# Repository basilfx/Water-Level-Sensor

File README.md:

# Water Level Sensor
Capacitive water level sensor based on a custom Arduino-based board.

## Introduction
This project started as an experiment to see if a water level sensor (with
fixed intervals) could be built, using the Arduino
[ADCTouch](https://github.com/martin2250/ADCTouch) library and capacitive
sensors. Capacitive sensors have the advantage that they can be isolated from
water, creating a water-tight sensor.

In this repository, you can find the CAD designs, firmware and 3D printed
parts to create a water level sensor.

## Features
* Small board that finds in a 19mm tube.
* 4 channels/board, can be daisy-chained up to 8 boards.
* I2C connection.
* Temperature sensor.

## Contents
* The `3d/` folder contains a 3D-printable designs for the necessary parts.
* The `applications/` folder contain applications and drivers that can interact
  with the sensor.
* The `firmware/` folder contains the Platform.IO-based firmware that runs on
  the sensors.
* The `pcb/` folder contains the Kicad schema and board design.

## My setup
Several proof of concepts have been built, to validate the idea and the
sensitivity of the setup in a 19mm PVC pipe (electrical conduit pipe). This
pipe was perfect for my 400 liter rain barrel, only occupying 0.5 L of water.

To create the fixed intervals, I 3D printed coils that I wound using 1.5 mm²
electrical wire. I could not get copper/aluminium tube that fitted exactly in
the 19mm tube, and this 'solution' somewhat expands against the inside of the
tube, ensuring as little as possible air between the tube and the coil.

In total, I used 4 sensor boards, connecting a total of 16 intervals, or
25 liter per interval. The picture below shows render of how one sensor board
is used for four intervals. Four of these assemblies are daisy-chained
together. The parent board is then connected to an external application to
read the sensor.

## License
The work in this repository is covered by CC BY-NC-SA 4.0. See the `LICENSE.md`
file for more information.

Some parts of this project are covered by a different license.

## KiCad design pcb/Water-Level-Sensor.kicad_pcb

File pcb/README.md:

# Water Level Sensor

## Pictures

## Schema
You can find the schema [here](Water-Level-Sensor.pdf).

## Mode of operation
The same board can operate in two modes:

* Parent mode
* Child mode

A chain of sensors (maximum of 7 + 1 sensors) exists out of one parent and zero
or more children. The parent will be the interface to the external application.
All children can be daisy-chained together.

```
[Application} <--> [Parent} <--> [Child 1] <--> [Child 2] <--> [Child 3]
```

Depending on the mode of operation, resistors R7-R10 must be populated
accordingly. All children are connected using a separate I2C bus.

The firmware uses R1-R3 and R11 for configuration. As of writing, the following
jumper resistors must be placed for the specific mode of operation.

| R1 | R2 | R3 | R11 | Description
|----|----|----|-----|--------------------------|
|    |    |    | X   | Parent mode, no children |
| X  |    |    | X   | Parent mode, 1 child     |
|    | X  |    | X   | Parent mode, 2 children  |
| X  | X  |    | X   | Parent mode, 3 children  |
|    |    |    |     | Child mode, first child  |
| X  |    |    |     | Child mode, second child |
|    | X  |    |     | Child mode, third child  |
| X  | X  |    |     | Child mode, fourth child |

## BOM
| Ref  | Value         | Footprint                                           | Farnell | DigiKey | Notes            |
|------|---------------|-----------------------------------------------------|---------|---------|------------------|
| C1   | 1µF           | Capacitor_SMD:C_0603_1608Metric                     |         |         |                  |
| C2   | 100nF         | Capacitor_SMD:C_0603_1608Metric                     |         |         |                  |
| C3   | 100nF         | Capacitor_SMD:C_0603_1608Metric                     |         |         |                  |
| C4   | 15pF          | Capacitor_SMD:C_0603_1608Metric                     |         |         |                  |
| C5   | 15pF          | Capacitor_SMD:C_0603_1608Metric                     |         |         |                  |
| R1   | 0             | Resistor_SMD:R_0603_1608Metric                      |         |         |                  |
| R2   | 0             | Resistor_SMD:R_0603_1608Metric                      |         |         |                  |
| R3   | 0             | Resistor_SMD:R_0603_1608Metric                      |         |         |                  |
| R4   | 10K           | Resistor_SMD:R_0603_1608Metric                      |         |         |                  |
| R5   | 4K7           | Resistor_SMD:R_0603_1608Metric                      |         |         |                  |
| R6   | 4K7           | Resistor_SMD:R_0603_1608Metric                      |         |         |                  |
| R7   | 0             | Resistor_SMD:R_0603_1608Metric                      |         |         | Parent-mode only |
| R8   | 0             | Resistor_SMD:R_0603_1608Metric                      |         |         | Parent-mode only |
| R9   | 0             | Resistor_SMD:R_0603_1608Metric                      |         |         | Child-mode only  |
| R10  | 0             | Resistor_SMD:R_0603_1608Metric                      |         |         | Child-mode only  |
| R11  | 0             | Resistor_SMD:R_0603_1608Metric                      |         |         |                  |
| U1   | ATmega328P-MU | Package_DFN_QFN:QFN-32-1EP_5x5mm_P0.5mm_EP3.1x3.1mm |         |         |                  |
| Y1   | 16MHz         | Crystal:Crystal_SMD_2016-4Pin_2.0x1.6mm             |         |         |                  |

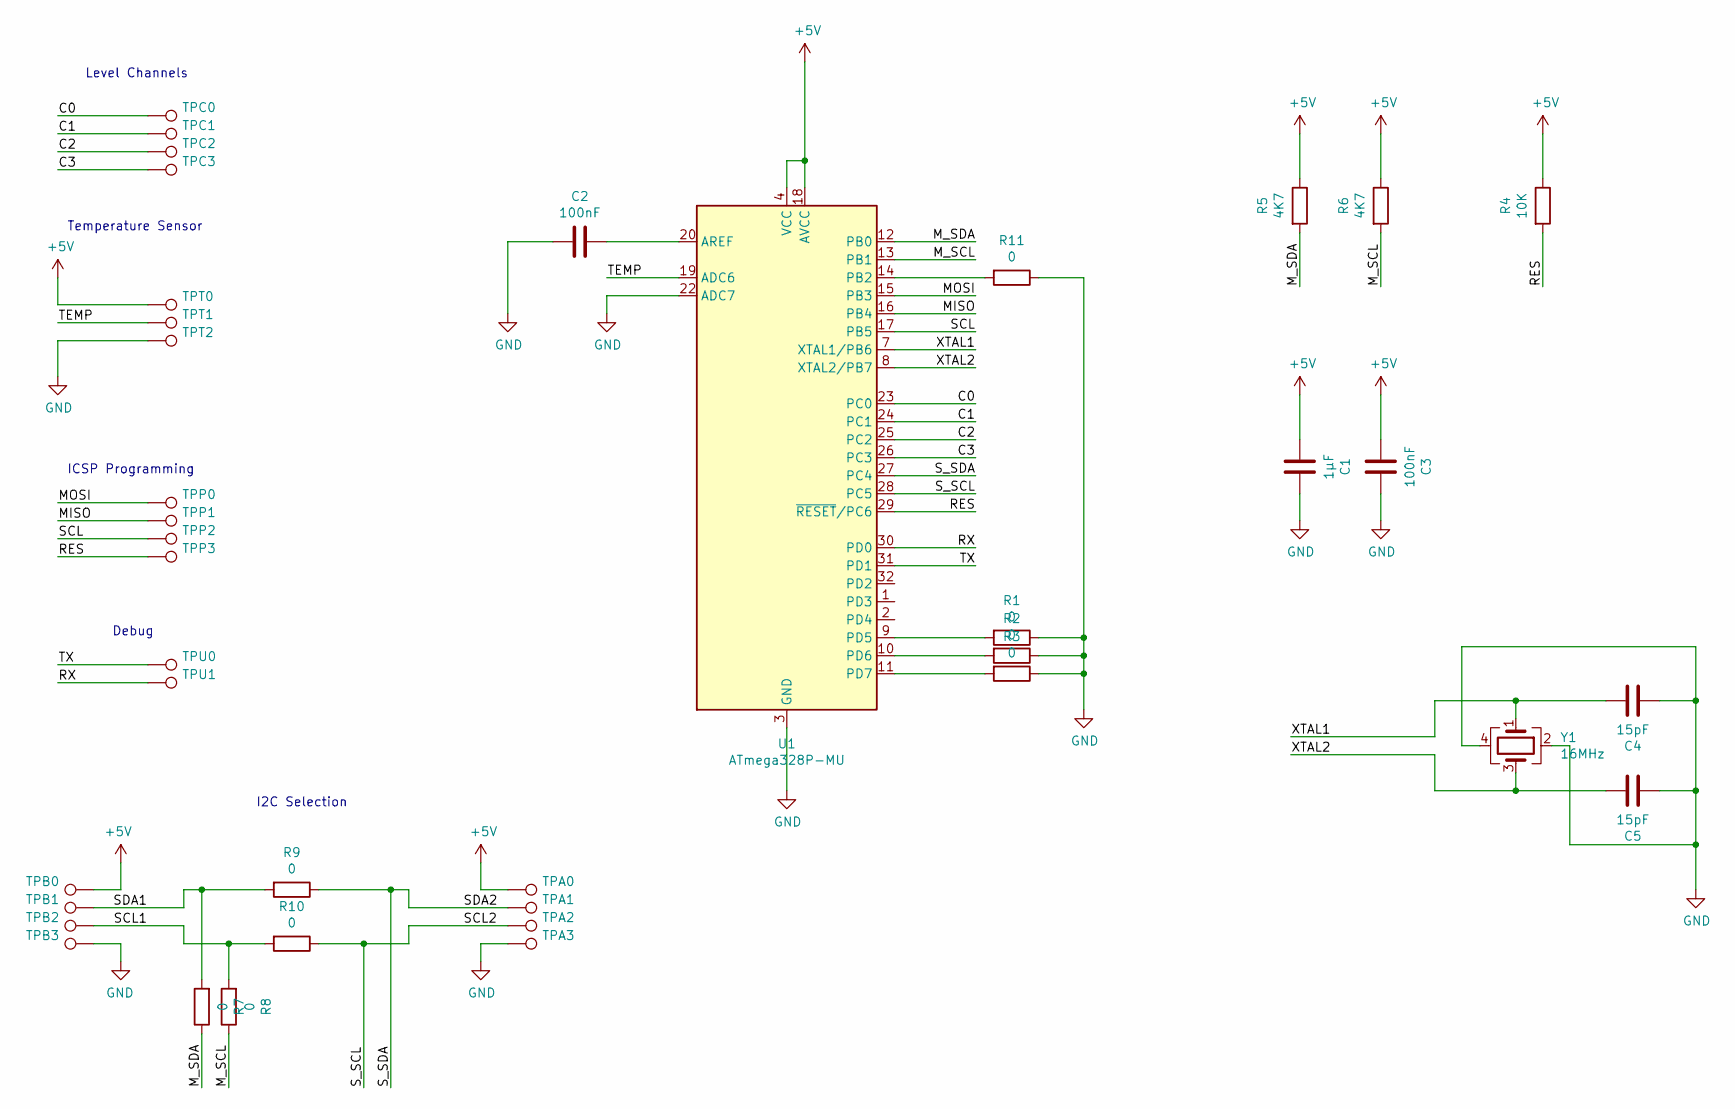
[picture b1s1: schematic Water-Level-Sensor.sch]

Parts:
C1: 1µF; C_0603_1608Metric
C2, C3: 100nF; C_0603_1608Metric
C4, C5: 15pF; C_0603_1608Metric
R1, R2, R3, R7, R8, R9, R10, R11: 0; R_0603_1608Metric
R4: 10K; R_0603_1608Metric
R5, R6: 4K7; R_0603_1608Metric
TPA0: 5V; TestPoint_Pad_D1.0mm
TPA1: SDA; TestPoint_Pad_D1.0mm
TPA2: SCL; TestPoint_Pad_D1.0mm
TPA3: GND; TestPoint_Pad_D1.0mm
TPB0: 5V; TestPoint_Pad_D1.0mm
TPB1: SDA; TestPoint_Pad_D1.0mm
TPB2: SCL; TestPoint_Pad_D1.0mm
TPB3: GND; TestPoint_Pad_D1.0mm
TPC0: C0; TestPoint_Pad_D1.0mm
TPC1: C1; TestPoint_Pad_D1.0mm
TPC2: C2; TestPoint_Pad_D1.0mm
TPC3: C3; TestPoint_Pad_D1.0mm
TPP0, TPP1, TPP2, TPP3: TestPoint; TestPoint_Pad_D1.0mm
TPT0, TPT1, TPT2: TestPoint; TestPoint_Pad_D1.0mm
TPU0: TX; TestPoint_Pad_D1.0mm
TPU1: RX; TestPoint_Pad_D1.0mm
U1: ATmega328P-MU; QFN-32-1EP_5x5mm_P0.5mm_EP3.1x3.1mm
Y1: 16MHz; Crystal_SMD_2016-4Pin_2.0x1.6mm

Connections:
+5V: C1.2, C3.2, R4.1, R5.1, R6.1, TPA0.1, TPB0.1, TPT0.1, U1.4 (VCC), U1.6 (VCC), U1.18 (AVCC)
/C0: TPC0.1, U1.23 (PC0)
/C1: TPC1.1, U1.24 (PC1)
/C2: TPC2.1, U1.25 (PC2)
/C3: TPC3.1, U1.26 (PC3)
/MISO: TPP1.1, U1.16 (PB4)
/MOSI: TPP0.1, U1.15 (PB3)
/M_SCL: R6.2, R8.1, U1.13 (PB1)
/M_SDA: R5.2, R7.1, U1.12 (PB0)
/RES: R4.2, TPP3.1, U1.29 (~RESET~/PC6)
/RX: TPU1.1, U1.30 (PD0)
/SCL: TPP2.1, U1.17 (PB5)
/SCL1: R8.2, R10.2, TPB2.1
/SCL2: R10.1, TPA2.1, U1.28 (PC5)
/SDA1: R7.2, R9.2, TPB1.1
/SDA2: R9.1, TPA1.1, U1.27 (PC4)
/TEMP: TPT1.1, U1.19 (ADC6)
/TX: TPU0.1, U1.31 (PD1)
/XTAL1: C4.1, U1.7 (XTAL1/PB6), Y1.1
/XTAL2: C5.1, U1.8 (XTAL2/PB7), Y1.3
GND: C1.1, C2.2, C3.1, C4.2, C5.2, R1.1, R2.1, R3.1, R11.1, TPA3.1, TPB3.1, TPT2.1, U1.3 (GND), U1.5 (GND), U1.21 (GND), U1.22 (ADC7), U1.33 (GND), Y1.2, Y1.4
unnamed: C2.1, U1.20 (AREF)
unnamed: R1.2, U1.9 (PD5)
unnamed: R2.2, U1.10 (PD6)
unnamed: R3.2, U1.11 (PD7)
unnamed: R11.2, U1.14 (PB2)

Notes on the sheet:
Level Channels
Temperature Sensor
ICSP Programming
Debug
I2C Selection

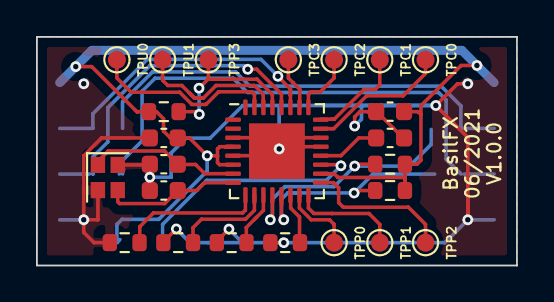
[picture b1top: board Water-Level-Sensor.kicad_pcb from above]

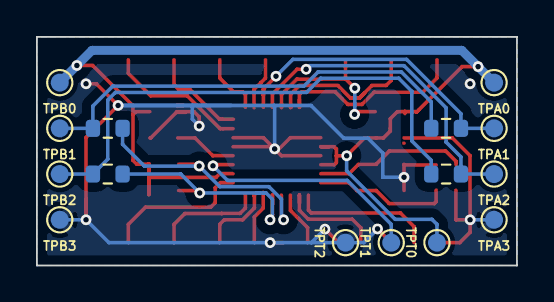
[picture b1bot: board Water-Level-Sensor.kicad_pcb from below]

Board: 2 copper layers, 26.7 x 12.7 mm, 39 parts (15 on the bottom side), 26 nets.

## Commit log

2021-09-20 Initial commit.
